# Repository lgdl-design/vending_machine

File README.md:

# Vending Machine

A coin-counting vending machine that uses flip-flop logic to count coins. It runs on a custom-built PCB and does not use a microcontroller.

## Hardware

- **Flip-Flops:** Basic sequential circuit components that provide memory. Used to count coins in the vending machine.
- **IR Sensor:** Detects a falling coin. It points at a black background and detects the change in color when a coin passes in front of it, which activates the counting circuit. A second IR sensor at the end of the machine detects when the object has been dispensed, which resets the counter.
- **L293D:** Motor driver that runs the motor for the wheel mechanism used to dispense objects.
- **5V DC Motor:** Spins the wheel mechanism to dispense the object.

## About The Machine

The vending machine was designed as a college project to demonstrate the use of flip-flops in practical circuits. We used a JK flip-flop based asynchronous counter. The IR sensor input drives the count up directly rather than a separate clock signal. The JK flip-flops also let us reset the counter using the IR sensor at the end of the machine once the object is dispensed.

The machine runs on a custom-built PCB that houses the logic components, including the gates, flip-flops, and the other parts that operate the rest of the machine. The PCB's output goes to a 7-segment display that shows the current coin count, and to the motor driver that drives the dispensing motor.

## Design

3D-printed body, designed in Autodesk Fusion:

## PCB

Designed in KiCAD and fabricated by toner transfer.

## Files

- 3D model (STL): [Vendo.stl](VendoDesign/Vendo.stl)
- PCB bottom copper layer (PDF): [VENDO-B_Cu.pdf](VendoPCB/VENDO-B_Cu.pdf)
- KiCAD project: [VENDO.kicad_pro](VendoPCB/VENDO.kicad_pro)

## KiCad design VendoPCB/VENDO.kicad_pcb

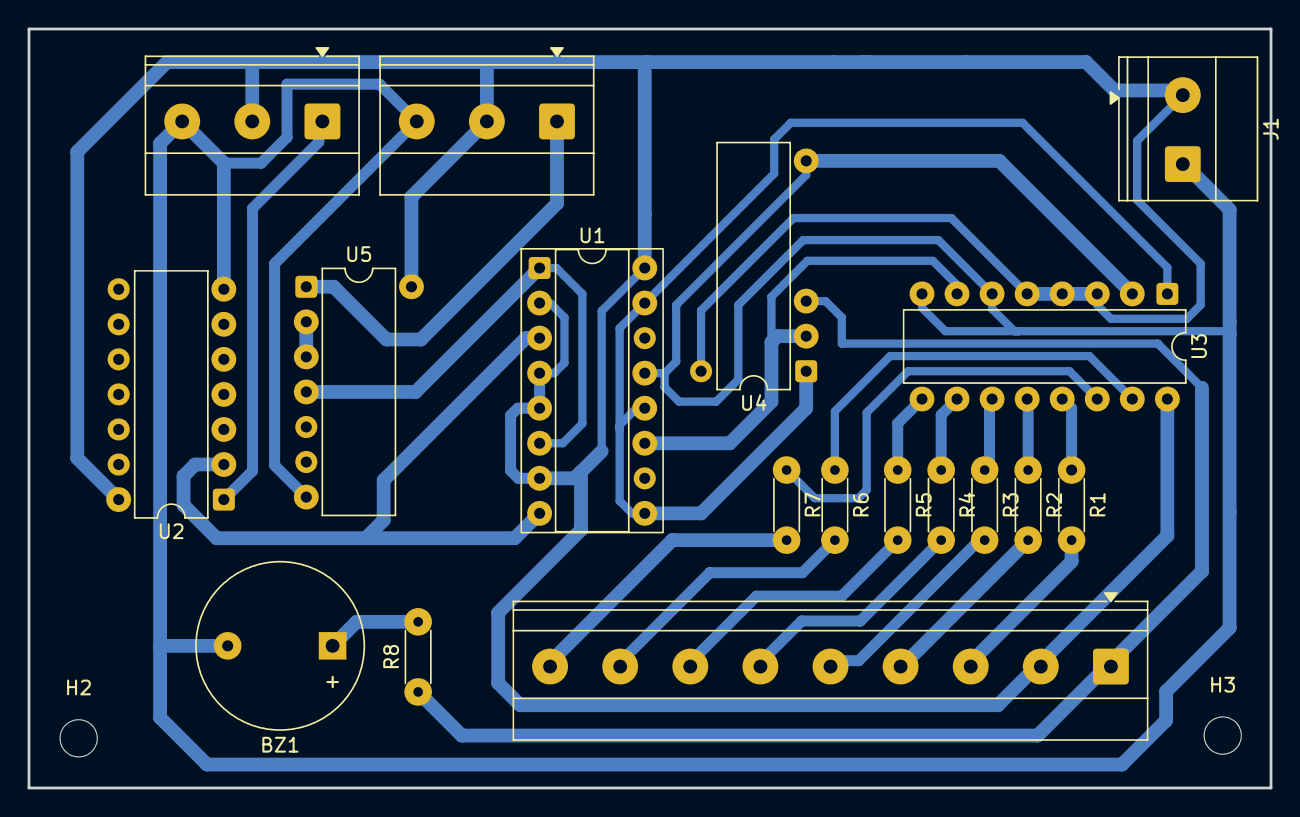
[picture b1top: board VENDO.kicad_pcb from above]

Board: 2 copper layers, 90.0 x 55.0 mm, 20 parts (0 on the bottom side), 25 nets.

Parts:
BZ1: Buzzer; Buzzer_12x9.5RM7.6
H2, H3: MountingHole; MountingHole_2.7mm
J1: Screw_Terminal_01x02; TerminalBlock_Phoenix_MKDS-1,5-2-5.08_1x02_P5.08mm_Horizont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
J2, J3: Screw_Terminal_01x03; TerminalBlock_Phoenix_MKDS-1,5-3-5.08_1x03_P5.08mm_Horizont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
J4: Screw_Terminal_01x08; TerminalBlock_Phoenix_MKDS-1,5-9-5.08_1x09_P5.08mm_Horizont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
R1, R2, R3, R4, R5, R6, R7, R8: R; R_Axial_DIN0204_L3.6mm_D1.6mm_P5.08mm_Horizontal
U1: 74LS76; DIP-16_W7.62mm_Socket
U2: 7404; DIP-14_W7.62mm
U3: 7447; DIP-16_W7.62mm
U4: 7408; DIP-14_W7.62mm
U5: 7414; DIP-14_W7.62mm

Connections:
unnamed: BZ1.1 (+), R8.2
unnamed: BZ1.2 (-), J1.2, J2.3, J3.3, U1.13 (GND), U2.7 (GND), U3.2 (C), U3.6 (D), U3.8 (GND), U4.7 (GND), U5.7 (GND)
unnamed: J1.1, J2.2, J3.2, J4.8 (7S), U1.2 (~S), U1.4 (J), U1.5 (PWR), U1.7 (~S), U1.16 (K), U2.14 (VCC), U3.3 (~LT), U3.4 (~BI), U3.5 (~RBI), U3.16 (VCC), U4.14 (VCC), U5.14 (VCC)
unnamed: J2.1, U5.1
unnamed: J3.1, U2.1
unnamed: J4.9 (MOT), R8.1, U4.3
unnamed: J4.1, R1.2
unnamed: J4.2, R2.2
unnamed: J4.3, R3.2
unnamed: J4.4, R4.2
unnamed: J4.5, R5.2
unnamed: J4.6, R6.2
unnamed: J4.7, R7.2
unnamed: U1.1 (C), U1.6 (C), U5.4 (OUT)
unnamed: U1.9 (J), U1.12 (K), U1.15 (Q), U3.1 (B), U4.1
unnamed: U1.3 (~R), U1.8 (~R), U2.2
unnamed: U1.11 (Q), U3.7 (A), U4.2
unnamed: R1.1, U3.13 (~a)
unnamed: R2.1, U3.12 (~b)
unnamed: R3.1, U3.11 (~c)
unnamed: R4.1, U3.10 (~d)
unnamed: R5.1, U3.9 (~e)
unnamed: R6.1, U3.15 (~f)
unnamed: R7.1, U3.14 (~g)
unnamed: U5.2, U5.3
